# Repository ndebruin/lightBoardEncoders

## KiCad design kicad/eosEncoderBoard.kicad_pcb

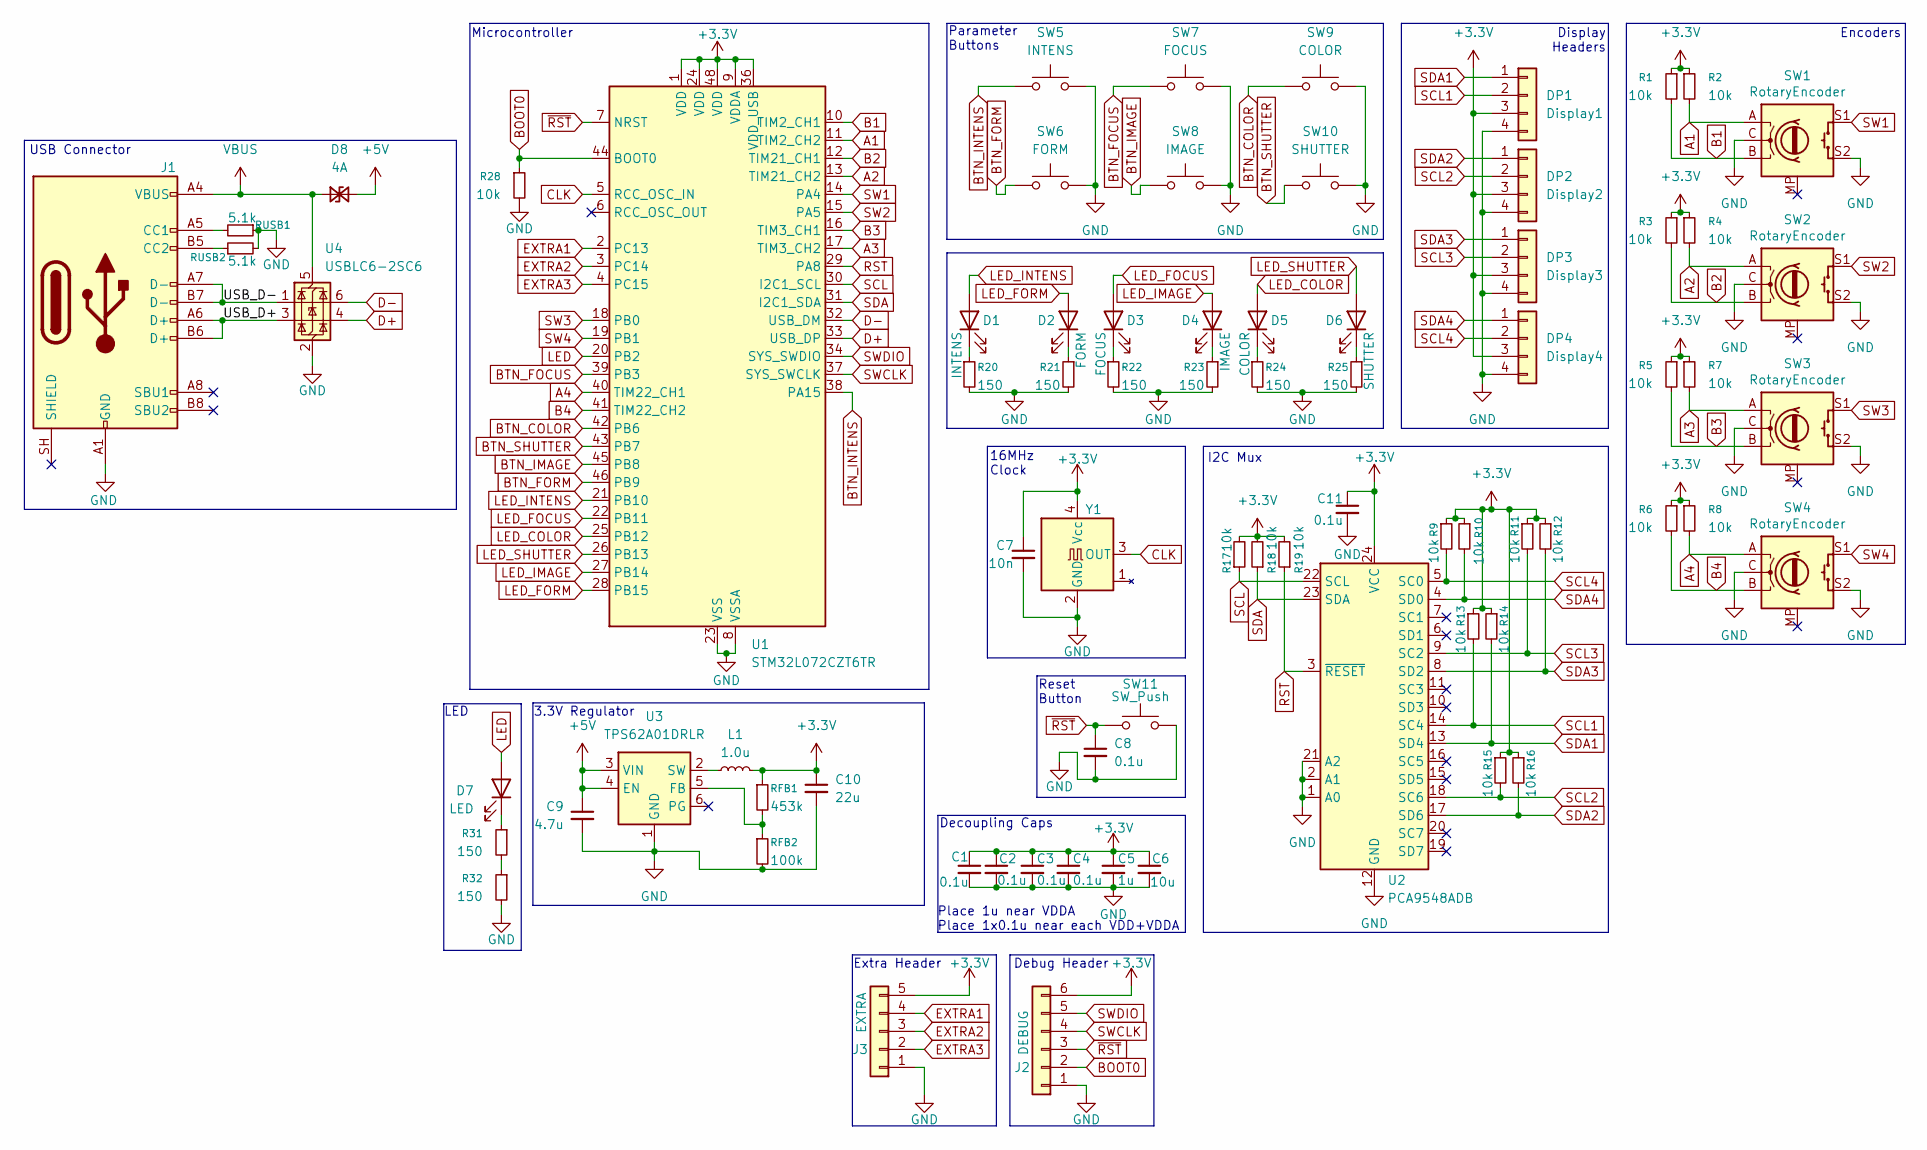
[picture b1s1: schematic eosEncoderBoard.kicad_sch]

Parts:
C1, C2, C3, C4, C8, C11: 0.1u; C_0603_1608Metric
C5: 1u; C_0603_1608Metric
C6: 10u; C_0603_1608Metric
C7: 10n; C_0603_1608Metric
C9: 4.7u; C_0603_1608Metric
C10: 22u; C_0603_1608Metric
D1: INTENS; LED_0603_1608Metric
D2: FORM; LED_0603_1608Metric
D3: FOCUS; LED_0603_1608Metric
D4: IMAGE; LED_0603_1608Metric
D5: COLOR; LED_0603_1608Metric
D6: SHUTTER; LED_0603_1608Metric
D7: LED; LED_0603_1608Metric
D8: 4A; D_SOD-923
DP1: Display1; PinHeader_1x04_P2.54mm_Vertical
DP2: Display2; PinHeader_1x04_P2.54mm_Vertical
DP3: Display3; PinHeader_1x04_P2.54mm_Vertical
DP4: Display4; PinHeader_1x04_P2.54mm_Vertical
J1: USB_C_Receptacle_USB2.0_16P; USB_C_Receptacle_GCT_USB4105-xx-A_16P_TopMnt_Horizontal
J2: DEBUG; PinSocket_1x06_P2.54mm_Vertical
J3: EXTRA; PinSocket_1x05_P2.54mm_Vertical
L1: 1.0u; L_1008_2520Metric
R1, R2, R3, R4, R5, R6, R7, R8, R9, R10, R11, R12, R13, R14, R15, R16, R17, R18, R19, R28: 10k; R_0603_1608Metric
R20, R21, R22, R23, R24, R25, R31, R32: 150; R_0603_1608Metric
RFB1: 453k; R_0603_1608Metric
RFB2: 100k; R_0603_1608Metric
RUSB1, RUSB2: 5.1k; R_0603_1608Metric
SW1, SW2, SW3, SW4: RotaryEncoder; RotaryEncoder_Alps_EC11E-Switch_Vertical_H20mm
SW5: INTENS; SW_Cherry_MX_PCB_1.00u_LED0603
SW6: FORM; SW_Cherry_MX_PCB_1.00u_LED0603
SW7: FOCUS; SW_Cherry_MX_PCB_1.00u_LED0603
SW8: IMAGE; SW_Cherry_MX_PCB_1.00u_LED0603
SW9: COLOR; SW_Cherry_MX_PCB_1.00u_LED0603
SW10: SHUTTER; SW_Cherry_MX_PCB_1.00u_LED0603
SW11: SW_Push; SW_Push_1P1T_XKB_TS-1187A
U1: STM32L072CZT6TR; LQFP-48_7x7mm_P0.5mm
U2: PCA9548ADB; SSOP-24_5.3x8.2mm_P0.65mm
U3: TPS62A01DRLR; SOT-563
U4: USBLC6-2SC6; SOT-23-6
Y1: OSC16M-3.3I/S3T; Oscillator_SMD_Abracon_ASE-4Pin_3.2x2.5mm

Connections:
+3.3V: C1.1, C2.1, C3.1, C4.1, C5.1, C6.1, C7.1, C10.1, C11.1, DP1.3, DP2.3, DP3.3, DP4.3, J2.6, J3.5, L1.2, R1.1, R2.1, R3.1, R4.1, R5.1, R6.1, R7.1, R8.1, R9.1, R10.1, R11.1, R12.1, R13.1, R14.1, R15.1, R16.1, R17.2, R18.2, R19.2, RFB1.1, U1.1 (VDD), U1.9 (VDDA), U1.24 (VDD), U1.36 (VDD_USB), U1.48 (VDD), U2.24 (VCC), Y1.4 (Vcc)
+5V: C9.1, D8.2 (A2), U3.3 (VIN), U3.4 (EN)
/USB_D+: J1.A6 (D+), J1.B6 (D+), U4.3 (I/O2)
/USB_D-: J1.A7 (D-), J1.B7 (D-), U4.1 (I/O1)
A1: R2.2, SW1.A, U1.11 (TIM2_CH2)
A2: R4.2, SW2.A, U1.13 (TIM21_CH2)
A3: R7.2, SW3.A, U1.17 (TIM3_CH2)
A4: R8.2, SW4.A, U1.40 (TIM22_CH1)
B1: R1.2, SW1.B, U1.10 (TIM2_CH1)
B2: R3.2, SW2.B, U1.12 (TIM21_CH1)
B3: R5.2, SW3.B, U1.16 (TIM3_CH1)
B4: R6.2, SW4.B, U1.41 (TIM22_CH2)
BOOT0: J2.2, R28.1, U1.44 (BOOT0)
BTN_COLOR: SW9.1, U1.42 (PB6)
BTN_FOCUS: SW7.1, U1.39 (PB3)
BTN_FORM: SW6.1, U1.46 (PB9)
BTN_IMAGE: SW8.1, U1.45 (PB8)
BTN_INTENS: SW5.1, U1.38 (PA15)
BTN_SHUTTER: SW10.1, U1.43 (PB7)
CLK: U1.5 (RCC_OSC_IN), Y1.3 (OUT)
D+: U1.33 (USB_DP), U4.4 (I/O2)
D-: U1.32 (USB_DM), U4.6 (I/O1)
EXTRA1: J3.4, U1.2 (PC13)
EXTRA2: J3.3, U1.3 (PC14)
EXTRA3: J3.2, U1.4 (PC15)
GND: C1.2, C2.2, C3.2, C4.2, C5.2, C6.2, C7.2, C8.2, C9.2, C10.2, C11.2, DP1.4, DP2.4, DP3.4, DP4.4, J1.A1 (GND), J1.A12 (GND), J1.B1 (GND), J1.B12 (GND), J2.1, J3.1, R20.2, R21.2, R22.2, R23.2, R24.2, R25.2, R28.2, R32.2, RFB2.2, RUSB1.1, RUSB2.2, SW1.C, SW1.S2, SW2.C, SW2.S2, SW3.C, SW3.S2, SW4.C, SW4.S2, SW5.2, SW6.2, SW7.2, SW8.2, SW9.2, SW10.2, SW11.1, U1.8 (VSSA), U1.23 (VSS), U1.35 (VSS), U1.47 (VSS), U2.1 (A0), U2.2 (A1), U2.12 (GND), U2.21 (A2), U3.1 (GND), U4.2 (GND), Y1.2 (GND)
LED: D7.2 (A), U1.20 (PB2)
LED_COLOR: D5.2 (A), U1.25 (PB12)
LED_FOCUS: D3.2 (A), U1.22 (PB11)
LED_FORM: D2.2 (A), U1.28 (PB15)
LED_IMAGE: D4.2 (A), U1.27 (PB14)
LED_INTENS: D1.2 (A), U1.21 (PB10)
LED_SHUTTER: D6.2 (A), U1.26 (PB13)
unnamed: D1.1 (K), R20.1
unnamed: D2.1 (K), R21.1
unnamed: D3.1 (K), R22.1
unnamed: D4.1 (K), R23.1
unnamed: D5.1 (K), R24.1
unnamed: D6.1 (K), R25.1
unnamed: D7.1 (K), R31.1
unnamed: J1.A5 (CC1), RUSB1.2
unnamed: J1.B5 (CC2), RUSB2.1
unnamed: R31.2, R32.1
unnamed: RFB1.2, RFB2.1, U3.5 (FB)
unnamed: L1.1, U3.2 (SW)
RST: R19.1, U1.29 (PA8), U2.3 (~RESET)
SCL: R17.1, U1.30 (I2C1_SCL), U2.22 (SCL)
SCL1: DP1.2, R13.2, U2.14 (SC4)
SCL2: DP2.2, R15.2, U2.18 (SC6)
SCL3: DP3.2, R11.2, U2.9 (SC2)
SCL4: DP4.2, R9.2, U2.5 (SC0)
SDA: R18.1, U1.31 (I2C1_SDA), U2.23 (SDA)
SDA1: DP1.1, R14.2, U2.13 (SD4)
SDA2: DP2.1, R16.2, U2.17 (SD6)
SDA3: DP3.1, R12.2, U2.8 (SD2)
SDA4: DP4.1, R10.2, U2.4 (SD0)
SW1: SW1.S1, U1.14 (PA4)
SW2: SW2.S1, U1.15 (PA5)
SW3: SW3.S1, U1.18 (PB0)
SW4: SW4.S1, U1.19 (PB1)
SWCLK: J2.4, U1.37 (SYS_SWCLK)
SWDIO: J2.5, U1.34 (SYS_SWDIO)
VBUS: D8.1 (A1), J1.A4 (VBUS), J1.A9 (VBUS), J1.B4 (VBUS), J1.B9 (VBUS), U4.5 (VBUS)
~RST: C8.1, J2.3, SW11.2, U1.7 (NRST)

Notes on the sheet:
USB Connector
Microcontroller
3.3V Regulator
Encoders
Reset Button
Parameter Buttons
Decoupling Caps
Debug Header
I2C Mux
Extra Header
Place 1u near VDDA Place 1x0.1u near each VDD+VDDA
LED
16MHz Clock
Display Headers

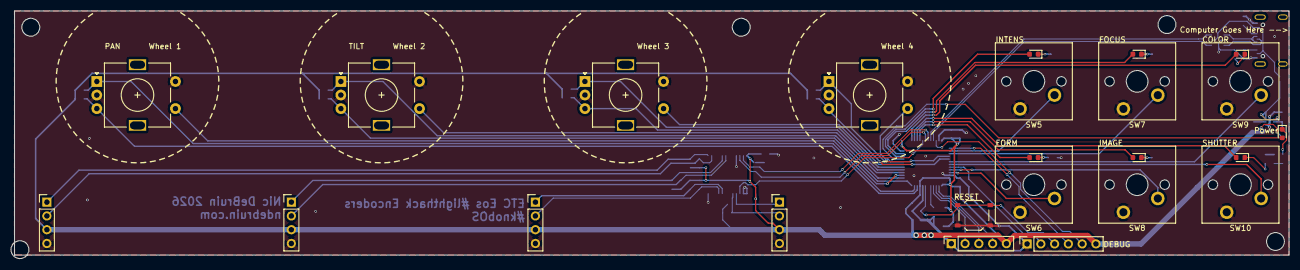
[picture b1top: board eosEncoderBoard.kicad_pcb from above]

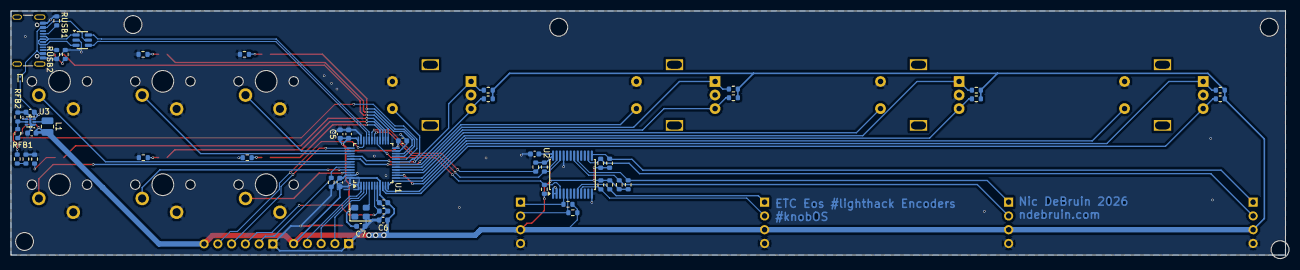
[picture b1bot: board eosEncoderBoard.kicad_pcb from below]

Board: 2 copper layers, 235.7 x 45.6 mm, 75 parts (51 on the bottom side), 64 nets.

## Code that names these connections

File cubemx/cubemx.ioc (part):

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Mcu.Name=STM32L072C(B-Z)Tx
Mcu.Package=LQFP48
Mcu.UserName=STM32L072CZTx
PA0.GPIOParameters=GPIO_Label
PA0.GPIO_Label=B1
PA0.Signal=S_TIM2_CH1
PA1.GPIOParameters=GPIO_Label
PA1.GPIO_Label=A1
PA1.Signal=S_TIM2_CH2
PA10.Mode=I2C
PA10.Signal=I2C1_SDA
PA11.Mode=Device
PA11.Signal=USB_DM
PA12.Mode=Device
PA12.Signal=USB_DP
PA13.Mode=Serial_Wire
PA13.Signal=SYS_SWDIO
PA14.Mode=Serial_Wire
PA14.Signal=SYS_SWCLK
PA15.GPIOParameters=GPIO_Label
PA15.GPIO_Label=BTN_INTENS
PA15.Signal=GPXTI15
PA2.GPIOParameters=GPIO_Label
PA2.GPIO_Label=B2
PA2.Signal=S_TIM21_CH1
PA3.GPIOParameters=GPIO_Label
PA3.GPIO_Label=A2
PA3.Signal=S_TIM21_CH2
PA4.GPIOParameters=GPIO_Label
PA4.GPIO_Label=SW1
PA4.Signal=GPXTI4
PA5.GPIOParameters=GPIO_Label
PA5.GPIO_Label=SW2
PA5.Signal=GPXTI5
PA6.GPIOParameters=GPIO_Label
PA6.GPIO_Label=B3
PA6.Signal=S_TIM3_CH1
PA7.GPIOParameters=GPIO_Label
PA7.GPIO_Label=A3
PA7.Signal=S_TIM3_CH2
PA8.GPIOParameters=GPIO_Label
PA8.GPIO_Label=RST
PA8.Signal=GPIO_Output
PA9.Mode=I2C
PA9.Signal=I2C1_SCL
PB0.GPIOParameters=GPIO_Label
PB0.GPIO_Label=SW3
PB0.Signal=GPXTI0
PB1.GPIOParameters=GPIO_Label
PB1.GPIO_Label=SW4
PB1.Signal=GPXTI1
PB10.GPIOParameters=GPIO_Label
PB10.GPIO_Label=LED_INTENS
PB10.Signal=GPIO_Output
PB11.GPIOParameters=GPIO_Label
PB11.GPIO_Label=LED_FOCUS
PB11.Signal=GPIO_Output
PB12.GPIOParameters=GPIO_Label
PB12.GPIO_Label=LED_COLOR
PB12.Signal=GPIO_Output
PB13.GPIOParameters=GPIO_Label
PB13.GPIO_Label=LED_SHUTTER
PB13.Signal=GPIO_Output
PB14.GPIOParameters=GPIO_Label
PB14.GPIO_Label=LED_IMAGE
PB14.Signal=GPIO_Output
PB15.GPIOParameters=GPIO_Label
PB15.GPIO_Label=LED_FORM
PB15.Signal=GPIO_Output
PB3.GPIOParameters=GPIO_Label
PB3.GPIO_Label=BTN_FOCUS
PB3.Signal=GPXTI3
PB4.GPIOParameters=GPIO_Label
PB4.GPIO_Label=A4
PB4.Signal=S_TIM22_CH1
PB5.GPIOParameters=GPIO_Label
PB5.GPIO_Label=B4
PB5.Signal=S_TIM22_CH2
PB6.GPIOParameters=GPIO_Label
PB6.GPIO_Label=BTN_COLOR
PB6.Signal=GPXTI6
PB7.GPIOParameters=GPIO_Label
PB7.GPIO_Label=BTN_SHUTTER
PB7.Signal=GPXTI7
PB8.GPIOParameters=GPIO_Label
PB8.GPIO_Label=BTN_IMAGE
PB8.Signal=GPXTI8
PB9.GPIOParameters=GPIO_Label
PB9.GPIO_Label=BTN_FORM
PB9.Signal=GPXTI9
PC13.GPIOParameters=GPIO_Label
PC13.GPIO_Label=EXTRA
PC13.Signal=GPIO_Output
PC14-OSC32_IN.GPIOParameters=GPIO_Label
PC14-OSC32_IN.GPIO_Label=EXTRA
PC14-OSC32_IN.Signal=GPIO_Output
PC15-OSC32_OUT.GPIOParameters=GPIO_Label
PC15-OSC32_OUT.GPIO_Label=EXTRA
PC15-OSC32_OUT.Signal=GPIO_Output
PH0-OSC_IN.Mode=HSE-External-Clock-Source
PH0-OSC_IN.Signal=RCC_OSC_IN
RCC.HSE_VALUE=16000000
RCC.SYSCLKFreq_VALUE=16000000
RCC.SYSCLKSource=RCC_SYSCLKSOURCE_HSI
board=custom

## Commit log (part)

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2025-07-25 display wrapper has been partially written
2025-07-27 comms class is being written. main thing rn is how to handle updates / dynamic sizing of parameter storage. something with the stack / heap?? need to do research
2025-07-28 eos communication got moved into a weird namespace thing so it effectively becomes a static class for callback reasons
2025-11-24 small fixes
2025-12-19 code for active-chan works, active-wheel does not
2025-12-20 data storage works!
2025-12-20 transmitting wheel position doesn't work for some reason. signing off 12-19
2025-12-20 TXing works!!!
2025-12-20 IT WORKS. prototype done, final version tbd
2025-12-20 update todo
2026-04-17 slight repo reformat & cleanup/comment changes.
2026-04-17 add blank kicad project for custom PCB
2026-04-17 schematic half done
2026-06-27 schematic basically done
2026-06-27 i dislike cubemx
2026-06-27 schematic done and code todo updated
2026-06-27 vscode git integration sucks
2026-06-28 more things to add to todo
2026-06-28 pcb started kinda
2026-06-28 pcb layout done, still need to handle silkscreen and add mounting holes and such
2026-06-29 pcb done other than silkscreen
2026-06-29 i can't measure
